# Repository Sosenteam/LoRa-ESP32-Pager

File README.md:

# LoRa-ESP32-Pager

This is a ESP-32 and SX1262 based pager, It contains full battery charging and management as well as an input keypad and encoder. It uses a 0.96" Oled (SSD1306).
There isn't any case because I wanted it to be a PCB only handheld (like the sprig), but I may laser cut a back when I get access to a laser cutter again (2 months).
The firmware is based on meshatastic, and hopefully will be able to use other meshtastic nodes to forward/mesh messages. 

I decided to build this because I felt like me and my friend group were too dependant on our phones, so I wanted to make a way to communicate that didn't involve phones. Also hopefully will be able to fully replace phones at school, which is aligned with my school possibly banning phones this upcoming year. The other main reason I wanted to start this project is because I wanted to learn more about radio and LoRa technology. This was also my first experience building my own PCBs, so I chose this over other projects because It would allow me to work with them.

|Name                   |Use                  |Qty|Total Price|Link                                                                               |
|-----------------------|---------------------|---|-----------|-----------------------------------------------------------------------------------|
|Oled Screen            |Screen               |5  |$9.80      |https://www.aliexpress.us/item/3256808552064563.html                               |
|Battery                |Battery              |5  |$23        |https://www.aliexpress.us/item/3256808031709894.html                               |
|                       |                     |   |           |                                                                                   |
|Ra-01SH                |LoRa                 |5  |16.9       |https://www.aliexpress.us/item/3256802374880132.html                               |
|MCP73871-2CCI/ML       |Battery Management   |5  |8.7        |https://www.aliexpress.us/item/3256809154370435.html                               |
|ESP32-S3-WROOM-1       |ESP32                |5  |20.6       |https://www.aliexpress.us/item/3256808569536766.html                               |
|TPS63001DRCR           |5v to 3v3            |5  |5.17       |https://www.aliexpress.us/item/3256806783602774.html (63001)                       |
|EC11E1834403           |Rotary Encoder       |5  |4.14       |https://www.aliexpress.us/item/2251832760130101.html                               |
|TYPE-C 16PIN 2MD(073)  |Usb Plug             |5  |2.69       |https://www.aliexpress.us/item/3256805314003507.html                               |
|All Resistors          |R100Ω                |   |4.74       |https://www.aliexpress.us/item/3256806810055728.html (Buy 2-3)                     |
|Inductor 0805 2.2uH    |Inductor for TPS63   |5  |1.45       |https://www.aliexpress.us/item/3256802926211468.html (2.2uH)                       |
|Leds                   |Battery Charge Leds  |10 |3.6        |https://www.aliexpress.us/item/2251832152971926.html                               |
|Diode 1N5819W          |Diode for Usb Power  |5  |0.23       |https://www.digikey.com/en/products/detail/tdk-corporation/MLP2012H2R2MT0S1/4327857|
|Ph2.0 Battery Connector|Battery Charger      |5  |1.45       |https://www.aliexpress.us/item/3256807255498839.html                               |
|PTS815SJM250SMTRLFS    |Reset and Boot Button|10 |1.15       |https://www.digikey.com/en/products/detail/c-k/PTS815SJM250SMTRLFS/9947846         |
|6x6 Tact Switch        |Keypad Buttons       |3  |1.29       |https://www.aliexpress.us/item/3256802301084670.html                               |
|Capacitor Set          |Decoupling           |1  |8.2        |https://www.aliexpress.us/item/3256807290577536.html (Buy 2-3)                     |
|Diode LESD             |ESD protection diodes|3  |3.34       |https://www.aliexpress.us/item/3256806903277344.html                               |
|Antenna                |Ra-01SH antenna      |5  |8.44       |https://www.aliexpress.us/item/3256805050972049.html                               |
|PCB                    |PCBs                 |5  |5          |                                                                                   |
|Ali Express Shipping   |                     |   |27         |                                                                                   |
|PCB Way Shipping       |                     |   |15         |                                                                                   |
|Digikey Shipping       |                     |   |7          |                                                                                   |
|                       |                     |   |$178.89    |                                                                                   |

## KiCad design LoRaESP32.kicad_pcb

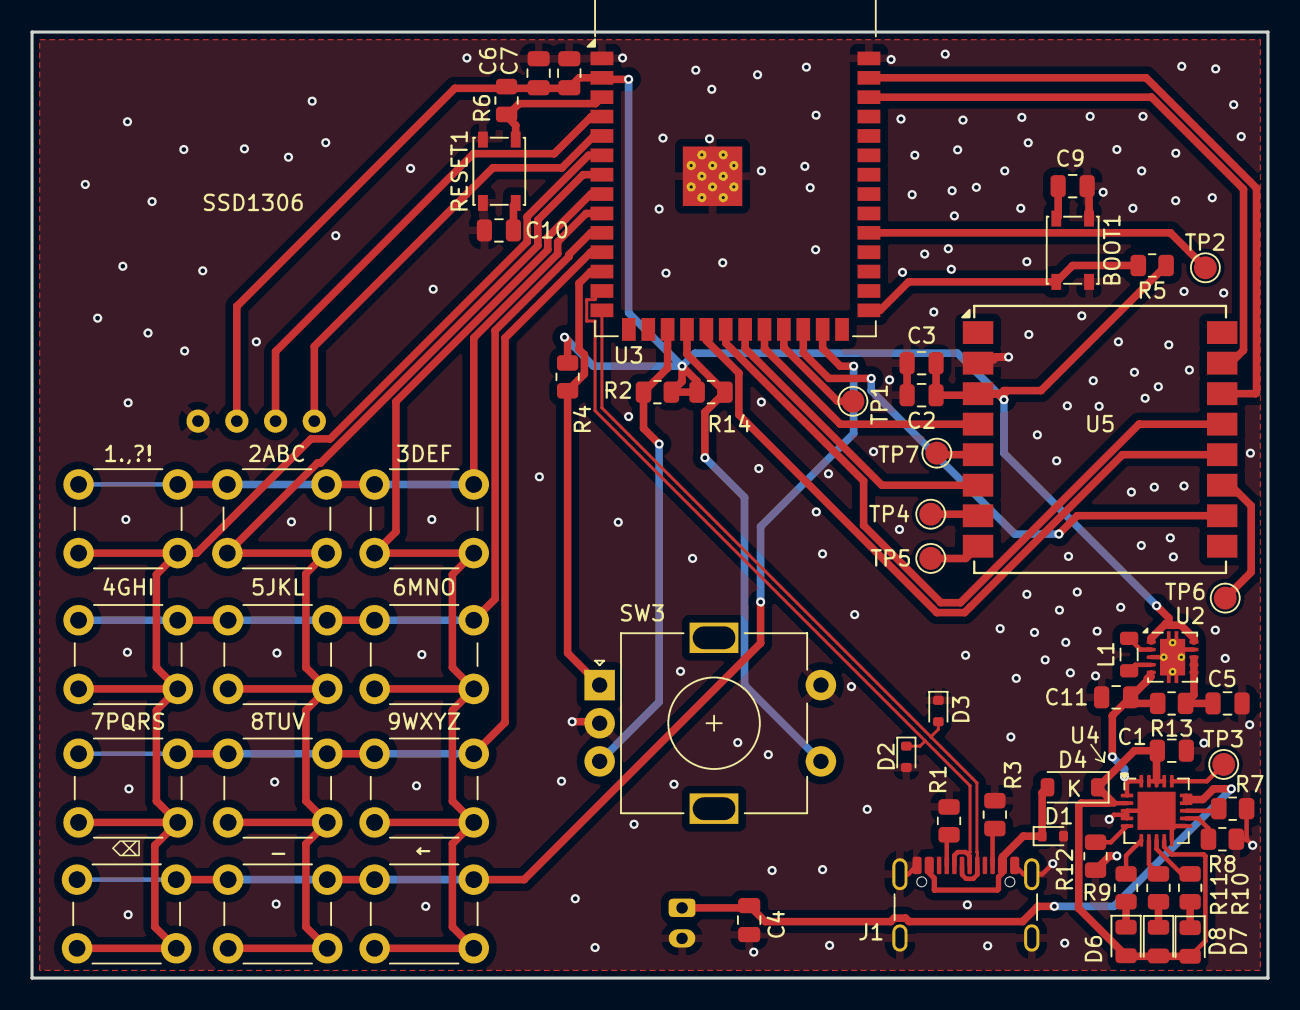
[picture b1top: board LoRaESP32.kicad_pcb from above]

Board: 2 copper layers, 81.0 x 62.0 mm, 61 parts (1 on the bottom side), 50 nets.

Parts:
1.,?!, 2ABC, 3DEF, 4GHI, 5JKL, 6MNO, 7PQRS, 8TUV, 9WXYZ: B3SL-1002P; SW_PUSH_6mm
BOOT1: PTS815SJM250SMTRLFS; SW_SPST_PTS810
BT1: B2B-PH-K-S(LF)(SN); JST_PH_B2B-PH-K_1x02_P2.00mm_Vertical
C1, C2, C7, C11: 0805W106K250CC; C_0805_2012Metric
C3, C5, C6, C9, C10: 0805B104K500BD; C_0805_2012Metric
C4: 0805B475K250CC; C_0805_2012Metric
D1, D2, D3: LESD5D5.0CT1G; D_SOD-523
D4: 1N5819W; D_SOD-123
D6: LS R976-NR-1-0-20-R18; LED_0805_2012Metric
D7, D8: LY R97xLG R971-KN-1-0-20-R18; LED_0805_2012Metric
J1: TYPE-C 16PIN 2MD(073); USB_C_Receptacle_GCT_USB4105-xx-A_16P_TopMnt_Horizontal
L1: MLP2012 MLP2012H2R2MT0S1; L_0805_2012Metric
R1, R3: RC0805JR-075K1L; R_0805_2012Metric
R2, R4, R5, R6, R7, R8, R12, R14: RMCF0805FT10K0; R_0805_2012Metric
R9, R10, R11: CRGCQ0805J470R; R_0805_2012Metric
R13: RC0805FR-07100RL; R_0805_2012Metric
RESET1: PTS815SJM250SMTRLFS; SW_SPST_PTS810
SSD1306: SSD1306
SW3: EC11E1834403; RotaryEncoder_Alps_EC11E-Switch_Vertical_H20mm
TP1: TEST_GPIO_21; TestPoint_Pad_D1.5mm
TP2: TEST_GPIO_38; TestPoint_Pad_D1.5mm
TP3: BatTest; TestPoint_Pad_D1.5mm
TP4: DIO2; TestPoint_Pad_D1.5mm
TP5: DIO3; TestPoint_Pad_D1.5mm
TP6: RXEN; TestPoint_Pad_D1.5mm
TP7: TXEN; TestPoint_Pad_D1.5mm
U2: TPS63001; Texas_DRC0010J_ThermalVias
U3: ESP32-S3-WROOM-1
U4: MCP73871-2CC; QFN-20-1EP_4x4mm_P0.5mm_EP2.5x2.5mm
U5: Ra-01SH; Ai-Thinker-Ra-01-LoRa
_: B3SL-1002P; SW_PUSH_6mm
←: B3SL-1002P; SW_PUSH_6mm
⌫: B3SL-1002P; SW_PUSH_6mm

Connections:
+3V3: C2.1, C3.1, C6.1, C7.1, R2.2, R4.1, R5.1, R6.1, R14.1, SSD1306.2 (VCC), U2.1 (VOUT), U2.10 (FB), U3.2 (3V3), U5.3 (VDD)
+5V: C1.1, D4.1 (K), D6.2 (A), D7.2 (A), D8.2 (A), U4.2 (VPCC), U4.9 (~TE), U4.17 (CE), U4.18 (IN), U4.19 (IN)
CHIP_PU: C10.2, R6.2, RESET1.2, U3.3 (EN)
Col1: 1.,?!.2, 4GHI.2, 7PQRS.2, U3.6 (IO6), ⌫.2
Col2: 2ABC.2, 5JKL.2, 8TUV.2, U3.7 (IO7), _.2
Col3: 3DEF.2, 6MNO.2, 9WXYZ.2, U3.8 (IO15), ←.2
D+: D3.2 (A2), J1.A6 (D+), J1.B6 (D+), U3.14 (IO20)
D-: D2.1 (A1), J1.A7 (D-), J1.B7 (D-), U3.13 (IO19)
EncoderA: R4.2, SW3.A, U3.12 (IO8)
EncoderB: R2.1, SW3.B, U3.17 (IO9)
EncoderSW: R14.2, SW3.S1, U3.18 (IO10)
GND: BOOT1.1, BT1.2 (-), C1.2, C2.2, C3.2, C4.1, C5.2, C6.2, C7.2, C9.1, C10.1, C11.1, D1.2 (A2), D2.2 (A2), D3.1 (A1), J1.A1 (GND), J1.A12 (GND), J1.B1 (GND), J1.B12 (GND), J1.S1 (SHIELD), R1.2, R3.2, R7.1, R8.1, R12.1, RESET1.1, SSD1306.1 (GND), SW3.C, SW3.S2, U2.3 (PGND), U2.9 (GND), U2.11 (PGND), U3.1 (GND), U3.40 (GND), U3.41 (GND), U4.3 (SEL), U4.4 (PROG2), U4.10 (V_{SS}), U4.11 (V_{SS}), U4.21 (V_{SS}), U5.2 (GND)
GPIO_0: BOOT1.2, C9.2, R5.2, U3.27 (IO0)
LoraBUSY: U3.24 (IO47), U5.10 (BUSY)
LoraDIO1: U3.21 (IO13), U5.6 (DIO1)
LoraMISO: U3.20 (IO12), U5.13 (MISO)
LoraMOSI: U3.39 (IO1), U5.14 (MOSI)
LoraNSS: U3.38 (IO2), U5.15 (~NSS)
LoraRST: U3.22 (IO14), U5.4 (~RESET)
LoraSCK: U3.19 (IO11), U5.12 (SCK)
unnamed: BT1.1 (+), C4.2, U4.14 (V_{BAT}), U4.15 (V_{BAT})
unnamed: D1.1 (A1), D4.2 (A), J1.A4 (VBUS), J1.A9 (VBUS), J1.B4 (VBUS), J1.B9 (VBUS)
unnamed: D6.1 (K), R9.2
unnamed: D7.1 (K), R10.2
unnamed: D8.1 (K), R11.1
unnamed: J1.A5 (CC1), R1.1
unnamed: J1.B5 (CC2), R3.1
unnamed: C5.1, R13.1, U2.6 (EN), U2.7 (PS/SYNC), U2.8 (VINA)
unnamed: L1.2, U2.4 (L1)
unnamed: L1.1, U2.2 (L2)
unnamed: C11.2, R13.2, U2.5 (VIN), U4.1 (OUT), U4.20 (OUT)
unnamed: TP1.1, U3.23 (IO21)
unnamed: TP2.1, U3.31 (IO38)
unnamed: R7.2, U4.13 (PROG1)
unnamed: R8.2, U4.12 (PROG3)
unnamed: R10.1, U4.8 (STAT1/~LBO)
unnamed: R11.2, U4.7 (STAT2)
unnamed: R12.2, U4.5 (THERM)
unnamed: TP3.1, U4.16 (V_{BAT_SENSE})
unnamed: R9.1, U4.6 (~PG)
unnamed: TP4.1, U5.7 (DIO2)
unnamed: TP5.1, U5.8 (DIO3)
unnamed: TP6.1, U5.11 (RXEN)
unnamed: TP7.1, U5.5 (TXEN)
OledSCL: SSD1306.3 (SCL), U3.4 (IO4)
OledSDA: SSD1306.4 (SDA), U3.5 (IO5)
Row1: 1.,?!.1, 2ABC.1, 3DEF.1, U3.9 (IO16)
Row2: 4GHI.1, 5JKL.1, 6MNO.1, U3.10 (IO17)
Row3: 7PQRS.1, 8TUV.1, 9WXYZ.1, U3.11 (IO18)
Row4: U3.25 (IO48), _.1, ←.1, ⌫.1

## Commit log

2025-07-11 Update JOURNAL.md
    6/27 to 7/5
2025-07-23 Fix PCB Layout Picture
